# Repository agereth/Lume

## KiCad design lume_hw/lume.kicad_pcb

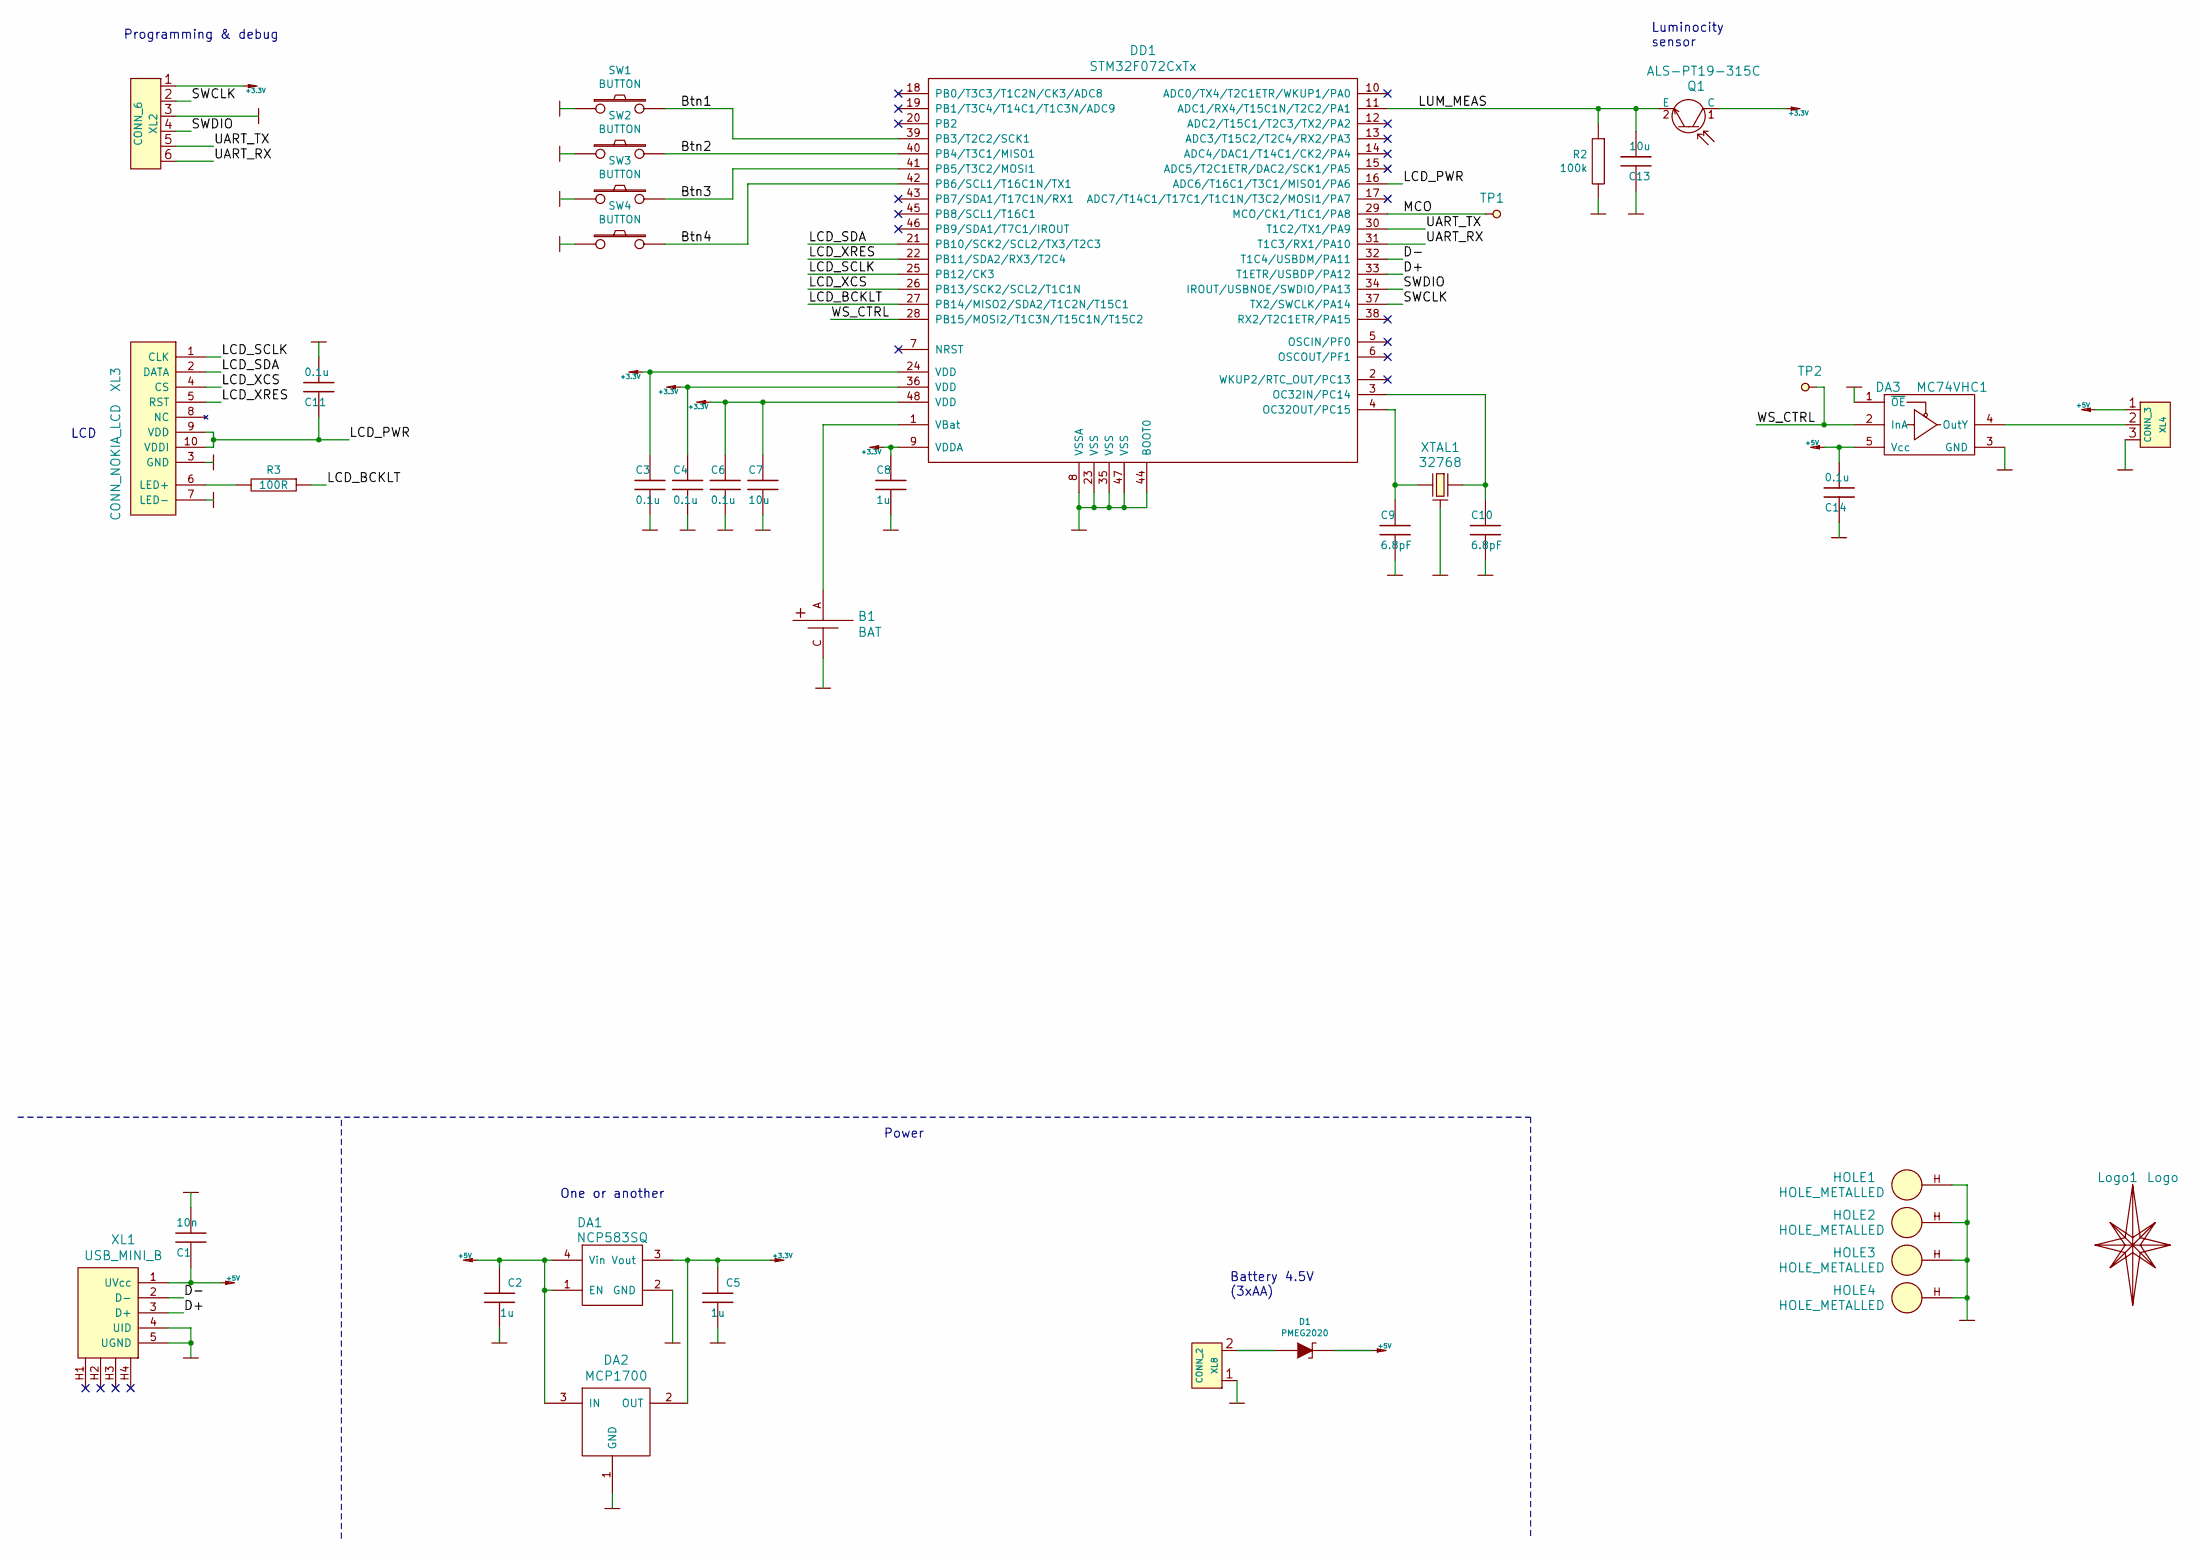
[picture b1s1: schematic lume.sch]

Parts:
B1: BAT; BATTERY_CH7410
C1: 10n; CAP_0603
C2, C5, C8: 1u; CAP_0603
C3, C4, C6, C11, C14: 0.1u; CAP_0603
C7, C13: 10u; CAP_0603
C9, C10: 6.8pF; CAP_0603
D1: PMEG2020; SOD323
DA1: NCP583SQ; SC82AB
DA2: MCP1700; SOT23-3
DA3: MC74VHC1; SOT23-5
DD1: STM32F072CxTx; LQFP48
HOLE1, HOLE2, HOLE3, HOLE4: HOLE_METALLED; Hole3_5_out6mm
Logo1: Logo; Ostranna_12d7_10d1
Q1: ALS-PT19-315C; RES_0603
R2: 100k; RES_0603
R3: 100R; RES_0603
SW1, SW2, SW3, SW4: BUTTON; BTN_6x6_4x4
TP1, TP2: TESTPOINT; TESTPOINT_1MM
XL1: USB_MINI_B; USBmicro_MOLEX_1050170001
XL2: CONN_6; PLS-6
XL3: CONN_NOKIA_LCD; NOKIA_10PIN
XL4: CONN_3; SLD_3_2D5
XL8: CONN_2; SLD_2_2D5
XTAL1: 32768; KX26

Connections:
+3.3V: C3.1, C4.1, C5.1, C6.1, C7.1, C8.1, DA1.3 (Vout), DA2.2 (OUT), DD1.9 (VDDA), DD1.24 (VDD), DD1.36 (VDD), DD1.48 (VDD), Q1.1 (C), XL2.1
+5V: C1.2, C2.1, C14.1, D1.C, DA1.1 (EN), DA1.4 (Vin), DA2.3 (IN), DA3.5 (Vcc), XL1.1 (UVcc), XL4.1
/Btn1: DD1.39 (PB3/T2C2/SCK1), SW1.2
/Btn2: DD1.40 (PB4/T3C1/MISO1), SW2.2
/Btn3: DD1.41 (PB5/T3C2/MOSI1), SW3.2
/Btn4: DD1.42 (PB6/SCL1/T16C1N/TX1), SW4.2
/D+: DD1.33 (T1ETR/USBDP/PA12), XL1.3 (D+)
/D-: DD1.32 (T1C4/USBDM/PA11), XL1.2 (D-)
/LCD_BCKLT: DD1.27 (PB14/MISO2/SDA2/T1C2N/T15C1), R3.1
/LCD_PWR: C11.1, DD1.16 (ADC6/T16C1/T3C1/MISO1/PA6), XL3.9 (VDD), XL3.10 (VDDI)
/LCD_SCLK: DD1.25 (PB12/CK3), XL3.1 (CLK)
/LCD_SDA: DD1.21 (PB10/SCK2/SCL2/TX3/T2C3), XL3.2 (DATA)
/LCD_XCS: DD1.26 (PB13/SCK2/SCL2/T1C1N), XL3.4 (CS)
/LCD_XRES: DD1.22 (PB11/SDA2/RX3/T2C4), XL3.5 (RST)
/LUM_MEAS: C13.1, DD1.11 (ADC1/RX4/T15C1N/T2C2/PA1), Q1.2 (E), R2.1
/MCO: DD1.29 (MCO/CK1/T1C1/PA8), TP1.1
/SWCLK: DD1.37 (TX2/SWCLK/PA14), XL2.2
/SWDIO: DD1.34 (IROUT/USBNOE/SWDIO/PA13), XL2.4
/UART_RX: DD1.31 (T1C3/RX1/PA10), XL2.6
/UART_TX: DD1.30 (T1C2/TX1/PA9), XL2.5
/WS_CTRL: DA3.2 (InA), DD1.28 (PB15/MOSI2/T1C3N/T15C1N/T15C2), TP2.1
GND: B1.C, C1.1, C2.2, C3.2, C4.2, C5.2, C6.2, C7.2, C8.2, C9.2, C10.2, C11.2, C13.2, C14.2, DA1.2 (GND), DA2.1 (GND), DA3.1 (~OE), DA3.3 (GND), DD1.8 (VSSA), DD1.23 (VSS), DD1.35 (VSS), DD1.44 (BOOT0), DD1.47 (VSS), HOLE1.H, HOLE2.H, HOLE3.H, HOLE4.H, R2.2, SW1.1, SW2.1, SW3.1, SW4.1, XL1.4 (UID), XL1.5 (UGND), XL2.3, XL3.3 (GND), XL3.7 (LED-), XL4.3, XL8.1, XTAL1.H
unnamed: B1.A, DD1.1 (VBat)
unnamed: C9.1, DD1.4 (OC32OUT/PC15), XTAL1.2
unnamed: C10.1, DD1.3 (OC32IN/PC14), XTAL1.1
unnamed: D1.A, XL8.2 (PM)
unnamed: DA3.4 (OutY), XL4.2 (PM)
unnamed: R3.2, XL3.6 (LED+)

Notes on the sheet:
Battery 4.5V (3xAA)
Luminocity sensor
LCD
Power
Programming & debug
One or another

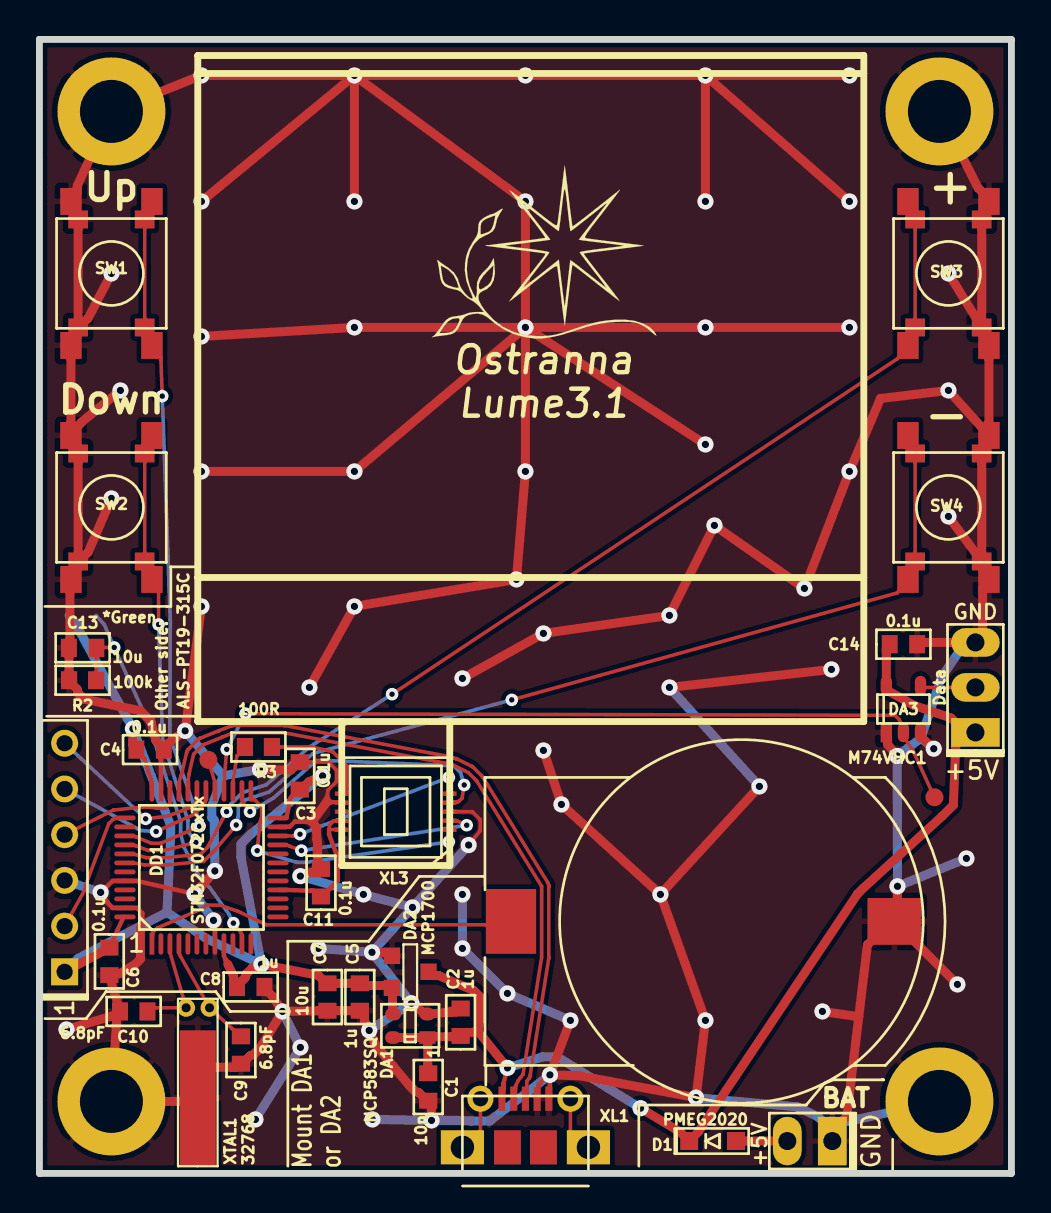
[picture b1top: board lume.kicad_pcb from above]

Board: 2 copper layers, 54.0 x 63.0 mm, 39 parts (1 on the bottom side), 28 nets.

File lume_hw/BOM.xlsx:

Reference | Value | Footprint | Quantity | PN | URL | Price | SolderPoints | SolderPointsDIP | Sum
B1 | BAT | Installation:BATTERY_CH7410 | 1 |  |  | 28 |  |  | 28
C1 | 10n | Capacitors:CAP_0603 | 1 |  |  | 0.5 |  |  | 0.5
C11 C14 C3 C4 C6 | 0.1u | Capacitors:CAP_0603 | 5 |  |  | 0.5 | 2 |  | 2.5
C13 C7 | 10u | Capacitors:CAP_0603 | 2 |  |  | 0.5 | 2 |  | 1
C2 C5 C8 | 1u | Capacitors:CAP_0603 | 3 |  |  | 0.5 | 2 |  | 1.5
C10 C9 | 6.8pF | Capacitors:CAP_0603 | 2 |  |  | 0.5 | 2 |  | 1
D1 | PMEG2020 | Diodes:SOD323 | 1 |  |  | 5 | 2 |  | 5
DA1 | NCP583SQ | SOT:SC82AB | 1 |  |  | 0 |  |  | 0
DA2 | MCP1700 | SOT:SOT23-3 | 1 | MCP1700T-3302E/TT |  | 10 | 3 |  | 10
DA3 | MC74VHC1 | SOT:SOT23-5 | 1 | M74VHC1GT125DT1G | https://www.terraelectronica.ru/catalog.php?ID=301&search=m7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 | 5.5 | 5 |  | 5.5
DD1 | STM32F072CxTx | LQFP_TQFP:LQFP48 | 1 | stm32f072c8t6 | http:// | 140 | 48 |  | 140
HOLE1 HOLE2 HOLE3 HOLE4 | HOLE_METALLED | PCB:Hole3_5_out6mm | 4 |  |  | 0 | 0 |  | 0
Logo1 | Logo | Pictures:Ostranna_12d7_10d1 | 1 |  |  | 0 |  |  | 0
Q1 | ALS-PT19-315C | Resistors:RES_0603 | 1 |  |  | 66 |  |  | 66
R2 | 100k | Resistors:RES_0603 | 1 |  |  | 0.5 | 2 |  | 0.5
R3 | 100R | Resistors:RES_0603 | 1 |  |  | 0.5 | 2 |  | 0.5
SW1 SW2 SW3 SW4 | BUTTON | BtnsSwitches:BTN_6x6_4x4 | 4 |  |  | 1 | 4 |  | 4
TP1 TP2 | TESTPOINT | PCB:TESTPOINT_1MM | 2 |  |  | 0 | 0 |  | 0
XL1 | USB_MINI_B | Connectors:USBmicro_MOLEX_1050170001 | 1 |  |  | 23 |  |  | 23
XL2 | CONN_6 | Connectors:PLS-6 | 1 |  |  | 2 |  | 6 | 2
XL3 | CONN_NOKIA_LCD | Connectors:NOKIA_10PIN | 1 |  |  | 100 |  |  | 100
XL4 | CONN_3 | Connectors:SLD_3_2D5 | 1 |  |  | 0 | 3 |  | 0
XL8 | CONN_2 | Connectors:SLD_2_2D5 | 1 |  |  | 0 |  |  | 0
XTAL1 | 32768 | Quartz:KX26 | 1 |  |  | 15 |  |  | 15
PCB |  |  | 1 |  |  | 430 |  |  | 430
Case |  |  | 1 |  |  | 500 |  |  | 500
Stones |  |  | 1 |  |  | 0 |  |  | 0
 |  |  |  |  |  |  |  | Итого | 1336

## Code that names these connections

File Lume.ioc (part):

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Mcu.Name=STM32F072C(8-B)Tx
Mcu.Package=LQFP48
Mcu.UserName=STM32F072C8Tx
PA1.Mode=IN1
PA1.Signal=ADC_IN1
PA10.Mode=Asynchronous
PA10.Signal=USART1_RX
PA13.Mode=Serial_Wire
PA13.Signal=SYS_SWDIO
PA14.Mode=Serial_Wire
PA14.Signal=SYS_SWCLK
PA8.Mode=Clock-out
PA8.Signal=RCC_MCO
PA9.Mode=Asynchronous
PA9.Signal=USART1_TX
PB10.Mode=Synchronous
PB10.Signal=USART3_TX
PB11.Mode=Synchronous
PB11.Signal=USART3_RX
PB12.Mode=Synchronous
PB12.Signal=USART3_CK
PB13.Mode=TX_Only_Simplex_Unidirect_Master
PB13.Signal=SPI2_SCK
PB14.Signal=S_TIM15_CH1
PB15.Mode=TX_Only_Simplex_Unidirect_Master
PB15.Signal=SPI2_MOSI
PB3.Signal=GPIO_Input
PB4.Signal=GPIO_Input
PB5.Signal=GPIO_Input
PB6.Signal=GPIO_Input
PC14-OSC32_IN.Mode=LSE-External-Oscillator
PC14-OSC32_IN.Signal=RCC_OSC32_IN
PC15-OSC32_OUT.Mode=LSE-External-Oscillator
PC15-OSC32_OUT.Signal=RCC_OSC32_OUT
RCC.HSE_VALUE=12000000
RCC.SYSCLKFreq_VALUE=8000000

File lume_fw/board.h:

/*
 * board.h
 *
 *  Created on: 01.02.2017
 *      Author: Kreyl
 */

#pragma once

#include <inttypes.h>

// ==== General ====
#define BOARD_NAME          "Lume3"
#define APP_NAME            "Lume"

// MCU type as defined in the ST header.
#define STM32F072xB     // no matter, 8 or B

// Freq of external crystal if any. Leave it here even if not used.
#define CRYSTAL_FREQ_HZ         12000000

#define SYS_TIM_CLK             (Clk.APBFreqHz)

#define SIMPLESENSORS_ENABLED   TRUE
#define BUTTONS_ENABLED         TRUE
#define ADC_REQUIRED            TRUE
#define I2C1_ENABLED            FALSE
#define I2C_USE_SEMAPHORE       FALSE

#if 1 // ========================== GPIO =======================================
// PortMinTim_t: GPIO, Pin, Tim, TimChnl, invInverted, omPushPull, TopValue

// Luminocity measurement
#define LUM_MEAS_PIN    GPIOA, 1

// Buttons
#define BTN1_PIN        GPIOB, 3, pudPullUp
#define BTN2_PIN        GPIOB, 4, pudPullUp
#define BTN3_PIN        GPIOB, 5, pudPullUp
#define BTN4_PIN        GPIOB, 6, pudPullUp

// LCD
#define LCD_SDA         GPIOB, 10
#define LCD_XRES        GPIOB, 11
#define LCD_SCLK        GPIOB, 12
#define LCD_XCS         GPIOB, 13
#define LCD_BCKLT       { GPIOB, 14, TIM15, 1, invNotInverted, omPushPull, 100 }

// Battery measurement
#define BAT_MEAS_PIN    GPIOA, 2

// UART
#define UART_GPIO       GPIOA
#define UART_TX_PIN     9
#define UART_RX_PIN     10

// LEDs
#define LEDWS_PIN       GPIOB, 15, omPushPull, pudNone, AF0, psHigh

#endif // GPIO

#if 1 // =========================== SPI =======================================
#define LEDWS_SPI       SPI2
#endif

#if 1 // ========================== USART ======================================
#define PRINTF_FLOAT_EN FALSE
#define CMD_UART        USART1
#define UART_USE_INDEPENDENT_CLK    TRUE
#define UART_TXBUF_SZ   1024

// LCD USART
#define LCD_UART_SPEED      100000
#endif

#if 1 // ========================== USB ========================================
#define USBDrv          USBD1   // USB driver to use

// CRS
#define CRS_PRESCALER   RCC_CRS_SYNC_DIV1
#define CRS_SOURCE      RCC_CRS_SYNC_SOURCE_USB
#define CRS_POLARITY    RCC_CRS_SYNC_POLARITY_RISING
#define CRS_RELOAD_VAL  ((48000000 / 1000) - 1) // Ftarget / Fsync - 1
#define CRS_ERROR_LIMIT 34
#define HSI48_CALIBRATN 32
#endif

#if ADC_REQUIRED // ======================= Inner ADC ==========================
#define ADC_MEAS_PERIOD_MS  450
// Clock divider: clock is generated from the APB2
#define ADC_CLK_DIVIDER     adcDiv2

// ADC channels
#define ADC_LUM_CHNL        1

#define ADC_VREFINT_CHNL    17  // All 4xx, F072 and L151 devices. Do not change.
#define ADC_CHANNELS        { ADC_LUM_CHNL, ADC_VREFINT_CHNL }
#define ADC_CHANNEL_CNT     2   // Do not use countof(AdcChannels) as preprocessor does not know what is countof => cannot check
#define ADC_SAMPLE_TIME     ast55d5Cycles
#define ADC_SAMPLE_CNT      8   // How many times to measure every channel

#define ADC_SEQ_LEN         (ADC_SAMPLE_CNT * ADC_CHANNEL_CNT)

#endif

#if 1 // =========================== DMA =======================================
#define STM32_DMA_REQUIRED  TRUE
// ==== Uart ====
#define UART_DMA_TX     STM32_DMA1_STREAM2
#define UART_DMA_RX     STM32_DMA1_STREAM3
#define UART_DMA_CHNL   0   // Dummy

#define LCD_DMA         STM32_DMA1_STREAM7  // USART3 TX

#define LEDWS_DMA       STM32_DMA1_STREAM5  // SPI2 TX

// ==== I2C1 ====
#define I2C1_DMA_TX     STM32_DMA1_STREAM2
#define I2C1_DMA_RX     STM32_DMA1_STREAM3
#define I2C1_DMA_CHNL   0 // Dummy

#if ADC_REQUIRED
#define ADC_DMA         STM32_DMA1_STREAM1
#define ADC_DMA_MODE    STM32_DMA_CR_CHSEL(0) |   /* dummy */ \
                        DMA_PRIORITY_LOW | \
                        STM32_DMA_CR_MSIZE_HWORD | \
                        STM32_DMA_CR_PSIZE_HWORD | \
                        STM32_DMA_CR_MINC |       /* Memory pointer increase */ \
                        STM32_DMA_CR_DIR_P2M |    /* Direction is peripheral to memory */ \
                        STM32_DMA_CR_TCIE         /* Enable Transmission Complete IRQ */
#endif // ADC

#endif // DMA

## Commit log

2015-08-26 First version of Lume - AVR based
2015-08-26 - AVR-based lume + ARM-based lume
2015-08-26 Switch to new kl_lib. Compiled, but not tested. UART not implemented.
2015-08-27 + Uart operational
2015-08-27 + LCD works
2015-08-28 + time counter
2015-08-28 * proceeding
2015-08-28 + Buttons + Interface seem working + Inc/Dec datetime
2015-08-29 * Backup reg settings moved to new file + PCA controlling fw in progress. Set individual/group brightness implemented.
2015-08-29 Seems ready to insert in case. Further Leds-Hours-Minutes accordances will be required.
2017-08-25 Something old
2017-08-25 + Lume3 sent to production
2017-09-17 + os 17.6.0 for f072 works
2017-09-17 + buttons
2017-09-17 - Brightness
2017-09-17 + RTC setup + RTC irq every second
2017-09-17 + Interface started + RTC works through reset
2017-09-17 proceeding
2017-09-18 Proceeding with menu + menu block sch
2017-09-18 1/5 of menu & interface
2017-09-18 + WS2812 LEDs * Sch: 100k instead of 10k at light sns
2017-09-18 + ADC tested * Luminocity sensor sch changed + New PCB sent to production
2017-09-19 + Display luminocity
2017-09-19 Menu design stopped at Day change
2017-09-29 + Menu completed + BOM
2017-09-29 * WKUP timer reconfigured to eliminate pause after setup
2017-10-01 + All may lit + Brightness depending on luminocity RC
2017-10-01 * Menu prolonged + Extra LED for 12 hours
2017-10-01 * Menu timeout prolonged
2017-10-03 crs system updated
2017-10-04 + Assembly cost
2017-10-07 Sanation
2017-10-07 Hangs at WakeupThd
2017-10-07 Wrong Hours cnt fixed
2017-11-20 Lume version with statemachines. Added state machine autogenerated code, events changed, practically all code from main.h/cpp moved to TimeSettins.h/cpp
2017-11-21 State machine added based on QPC framework Settings and mimor functions moved from main.cpp/h to TimeSettings.cpp/h Two screens instead of one made
2017-11-27 state machines on QPC framework added event handlers from main.cpp/h moved to EventHandlers.cpp/h main.cpp refactored
2017-11-27 changes to interface.h and kl_time (another event ID)
2017-11-27 small refactoring
2017-12-02 new qpc framework and new statechart
2017-12-02 update framwork + unpdated diagram (corrent entry events used)
2017-12-02 +correct diagram
2017-12-02 back to state machine with 1 screen new qpc.h by Ilya Tagunov new correct ctate machine diagram
